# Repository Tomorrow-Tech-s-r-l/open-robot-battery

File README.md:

# ⚡ Open Robot Battery (ORB)

*An open-source power delivery module for makers and robotics, powered by Amperry powerbanks.*

*Humanoid robot powered by the ORB module.*

*Four-wheeled warehouse robot with ORB battery module.*

*Front PCB view.*

*Back PCB view.*

*ORB inverter-turtle prototype with power inverter integration.*

*ORB development kit prototype for mobile robot applications.*

---

## 📖 Introduction

The **Open Robot Battery** (codename **ORB**) is an open-source hardware module designed to power up robots, IoT devices, drones, and prototypes.  

It works with **Amperry powerbanks**, which are charged inside Amperry stations, and provides makers, startups, and research labs with a flexible, safe, and modular way to bring portable energy into their projects.  

> ⚠️ **Important**: To use ORB you need an **Amperry-compatible powerbank**, which must be purchased together with an Amperry station. The ORB module is open-source, but the powerbanks remain proprietary.

---

## 🚀 Features

- ✅ Open hardware design for makers, startups, and research labs  
- ✅ Modular connection system (pogo pins, solenoid lock)  
- ✅ Flexible output: USB-C PD, robotics connectors (XT30/XT60), barrel jacks, etc.  
- ✅ Adaptable form factor – attach to robots, kiosks, IoT devices  
- ✅ Safe and tested with Amperry powerbanks  

---

## 🔌 How It Works
[ Amperry Station ] → [ Powerbank ] → [ ORB Module ] → [ Your Device ]

1. Powerbanks are charged inside the **Amperry station**.  
2. The charged powerbank is docked into the **ORB module**.  
3. ORB adapts the energy and delivers it to your device via your preferred connector.  

---

## 📦 Hardware Requirements

- **Required**: Amperry powerbank (purchase with a station from [Amperry](https://amperry.me))  
- Supported power levels:  
  - 5V (USB devices, IoT sensors)  
  - 12V (embedded boards, routers)  
  - 20V (robots, laptops, drones)  
- Connectors: USB-C PD, XT60, barrel jack, GPIO headers (customizable)  

---

## 🛠 Getting Started

1. Order an **Amperry powerbank + station**.  
2. Clone/download this repository.  
3. Access the **hardware files** in the `hardware/` folder:
   - Review the **schematics** (`hardware/schematics/LANDER_schematics.pdf`)
   - Check the **BOM** (`hardware/bom/LANDER_BOM.csv`) for component sourcing
   - Download **gerber files** (`hardware/gerber/LANDER-gerber-files.zip`) for PCB manufacturing
   - Use **CAD files** (`hardware/cad/LANDER_project_311025.zip`) for mechanical design and KiCad source files
4. Build or 3D-print the ORB module.  
5. Add the connectors your project requires.  
6. Plug in your powerbank and start powering your device.

## 🔧 Using with KiCad

The ORB project includes complete KiCad source files for both schematics and PCB layout. Follow these steps to open and work with the project in KiCad:

### Opening the KiCad Project

1. **Extract the CAD files**:
   ```bash
   cd hardware/cad
   unzip LANDER_project_311025.zip
   ```

2. **Open in KiCad**:
   - Launch KiCad (version 8.0 or later recommended)
   - Go to **File → Open Project**
   - Navigate to the extracted folder and open `Amperry_robot.kicad_pro`

3. **Project Structure**:
   The KiCad project contains:
   - `Amperry_robot.kicad_sch` - Main schematic file
   - `inputs_sheet.kicad_sch` - Input section schematic
   - `mech_conn_sheet.kicad_sch` - Mechanical connector section schematic
   - `Amperry_robot.kicad_pcb` - PCB layout file

### Viewing Schematics

- Click **Open Schematic** (or press `Ctrl+E`) to view the electrical schematics
- The project uses hierarchical sheets - navigate between sheets using the **Hierarchy Navigator** (press `Ctrl+H`)
- Use the **Properties** panel (press `E` on a component) to view component details

### Viewing PCB Layout

- Click **Open PCB Editor** (or press `Ctrl+P`) to view the PCB layout
- Use **3D Viewer** (press `Alt+3`) to see a 3D visualization of the board
- Switch between front and back layers using the layer selector

### Making Modifications

1. **Before making changes**, create a new branch or fork the repository
2. **Modify schematics** as needed:
   - Add/remove components
   - Adjust component values
   - Modify connections
3. **Update PCB layout** if schematic changes affect the board:
   - Run **Tools → Update PCB from Schematic** (or press `F8`) to sync changes
   - Adjust component placement and routing as needed
4. **Generate new Gerber files**:
   - Go to **File → Fabrication Outputs → Gerbers**
   - Select all layers and click **Generate Drill Files**
   - Export files for manufacturing

### Exporting for Manufacturing

1. **Generate Gerbers**:
   - File → Fabrication Outputs → Gerbers
   - Ensure all layers are selected (F.Cu, B.Cu, F.Silkscreen, B.Silkscreen, F.Mask, B.Mask, Edge.Cuts)
   - Generate drill files (PTH and NPTH)

2. **Generate BOM**:
   - File → Fabrication Outputs → BOM
   - Export as CSV or use the built-in BOM tool

3. **Create 3D Model**:
   - File → Export → STEP
   - Useful for mechanical integration

### Tips for Contributors

- Always run **Electrical Rules Check** (ERC) before committing changes (Tools → ERC)
- Run **Design Rules Check** (DRC) for PCB changes (Tools → DRC)
- Keep component libraries updated
- Document any significant changes in commit messages
- Test schematic changes by regenerating and reviewing the PDF export

## 📋 Documentation

- **[Technical Manual](MANUAL.md)** - Complete technical documentation including assembly instructions, safety warnings, and usage guidelines
- **[Hardware Files](hardware/)** - All hardware design files organized by type:
  - **[Schematics](hardware/schematics/)** - Electrical schematics in PDF format
  - **[Gerber Files](hardware/gerber/)** - PCB manufacturing files
  - **[Bill of Materials](hardware/bom/)** - Complete BOM in CSV format
  - **[CAD Files](hardware/cad/)** - KiCad source files (.kicad_sch, .kicad_pcb), 3D mechanical models (STEP), and Gerber files
  - **[Images](images/)** - Project images and diagrams  

---

## 💡 Example Use Cases

- 🤖 Robotics platforms and mobile robots  
- 🚁 Drones and UAVs  
- 🌐 IoT devices and field instruments  
- 🏫 University labs and prototyping kits  
- 🖥 Portable kiosks and installations  

---

## 📜 License & Usage Rules

- ORB is released as **open-source hardware** (license: [CC BY-NC-SA]).  
- **Restrictions**:  
  - The **Amperry powerbank hardware is proprietary** and must be purchased from Amperry.  
  - Usage in **powerbank rental systems** is exclusive to Amperry.  
  - Usage in **defense or weapons applications** requires prior approval and a special license.  

- For complete license details, see [LICENSE.md](LICENSE.md).
---

## 🤝 Contributing

We welcome contributions from the community! Here's how you can help improve the Open Robot Battery project.

### How to Contribute

1. **Report Issues**:
   - Found a bug or have a suggestion? Open an issue on GitHub
   - Include as much detail as possible: steps to reproduce, expected vs actual behavior, relevant files

2. **Improve Documentation**:
   - Fix typos or clarify instructions
   - Add missing information or examples
   - Translate documentation to other languages
   - Improve code comments and docstrings

3. **Hardware Improvements**:
   - **KiCad Project**: Modify schematics or PCB layout using the provided KiCad files
     - Extract the CAD files from `hardware/cad/LANDER_project_REV_DATE.zip` to work on them
     - Make changes in a new branch
     - Run ERC (Electrical Rules Check) and DRC (Design Rules Check) before submitting
     - Export updated Gerber files and update the repository
     - **Before committing**: Re-zip the CAD project folder and delete the unzipped folder
       ```bash
       cd hardware/cad
       zip -r LANDER_project_REV_DATE.zip [extracted_folder_name]/
       rm -rf [extracted_folder_name]/
       ```
     - Only commit the `.zip` file, not the extracted project files
     - This keeps the repository clean and prevents versioning conflicts with KiCad temporary files
   - **Mechanical Design**: Improve casing, mounting options, or add new connector configurations
   - **Component Selection**: Suggest better components or alternatives in the BOM

4. **Submit Pull Requests**:
   - Fork the repository
   - Create a feature branch (`git checkout -b feature/amazing-feature`)
   - Make your changes and test thoroughly
   - Commit with clear messages (`git commit -m 'Add amazing feature'`)
   - Push to your fork (`git push origin feature/amazing-feature`)
   - Open a Pull Request with a clear description of changes

### Contribution Guidelines

- **Code/Hardware Changes**:
  - Follow existing project structure and naming conventions
  - Ensure all tests pass (if applicable)
  - Update documentation for any new features
  - Run ERC/DRC checks for KiCad changes

- **Documentation**:
  - Use clear, concise language
  - Include examples where helpful
  - Update the README if adding new features

- **Pull Request Process**:
  - Keep PRs focused on a single feature or fix
  - Reference related issues in your PR description
  - Be responsive to feedback and requested changes

### Areas Where We Need Help

- 🐛 **Bug Fixes**: Test the design and report any issues
- 🔌 **New Connectors**: Add support for additional connector types
- 📐 **Mechanical Designs**: Improve casing, mounting solutions, or create 3D printable parts
- 🌍 **Translations**: Translate documentation to other languages
- 📚 **Examples**: Create example projects and use cases
- 🔬 **Testing**: Test designs with different powerbanks and report results

### Share Your Projects

We love seeing what people build with ORB! Share your projects:
- Open an issue with photos and description
- Tag us on social media
- Contribute to the gallery section

Thank you for contributing to open-source hardware! 🎉  

---

## 🌍 Community & Contact

- 🌐 Website: [https://tomorrowtech.it/open-robot-battery.html](https://amperry.me)  
- ✉️ Email: sviluppo@tomorrowtech.it  

---

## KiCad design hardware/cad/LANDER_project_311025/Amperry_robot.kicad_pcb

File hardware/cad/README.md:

# CAD Files

This folder contains the mechanical design files for the Open Robot Battery (LANDER) project.

## Files

- `LANDER-CAD-files.zip` - Complete CAD package containing 3D mechanical models and source files for the LANDER module
- `LANDER-mechanical.step` - 3D mechanical model in STEP format [TODO]
- `LANDER-mechanical.stl` - 3D printable files for prototyping [TODO]

## Mechanical Features

- Powerbank docking mechanism
- Spring ejector system
- Solenoid mounting points
- Connector mounting areas
- Heat dissipation considerations

## 3D Printing

STL files are provided for rapid prototyping and testing of mechanical components.

> **Note**: Replace this README with actual CAD files when available.

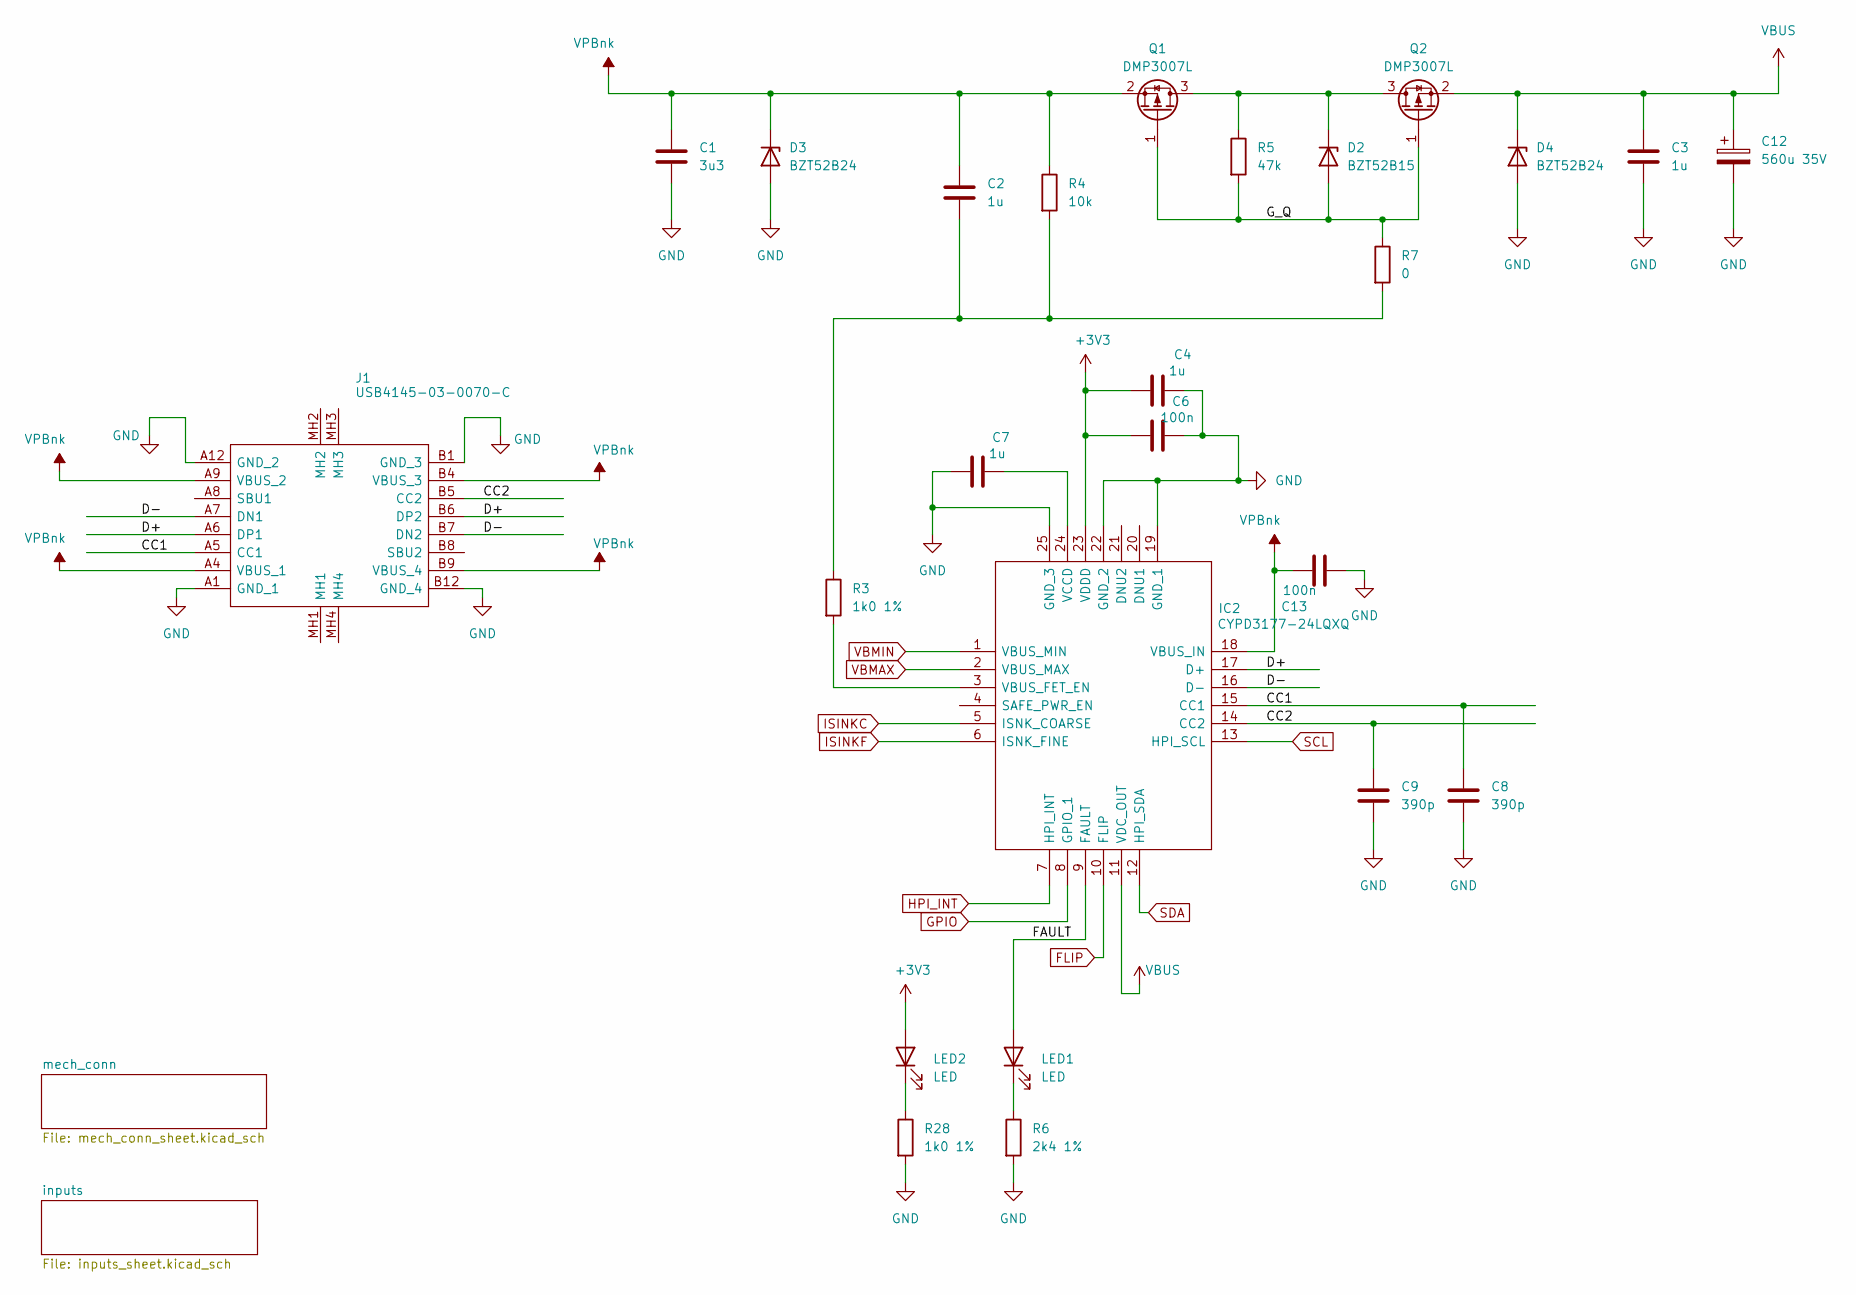
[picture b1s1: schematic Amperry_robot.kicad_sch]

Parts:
C1: 3u3; C_1206_3216Metric_Pad1.33x1.80mm_HandSolder
C2, C3, C4, C7: 1u; C_1206_3216Metric_Pad1.33x1.80mm_HandSolder
C6, C13: 100n; C_1206_3216Metric_Pad1.33x1.80mm_HandSolder
C8, C9: 390p; C_1206_3216Metric_Pad1.33x1.80mm_HandSolder
C12: 560u 35V; CP_Elec_10x10.5
D2: BZT52B15; D_SOD-123F
D3, D4: BZT52B24; D_SOD-123F
IC2: CYPD3177-24LQXQ; QFN50P400X400X60-25N-D; Manufacturer_Part_Number CYPD3177-24LQXQ; Mouser Part Number 727-CYPD3177-24LQXQ
J1: USB4145-03-0070-C; USB4145030070C; Manufacturer_Part_Number USB4145-03-0070-C; Mouser Part Number 640-USB4145-3-0070-C
LED1, LED2: LED; LED_0805_2012Metric_Pad1.15x1.40mm_HandSolder
Q1, Q2: DMP3007L; TO-252-2
R3, R28: 1k0 1%; R_1206_3216Metric_Pad1.30x1.75mm_HandSolder
R4: 10k; R_1206_3216Metric_Pad1.30x1.75mm_HandSolder
R5: 47k; R_1206_3216Metric_Pad1.30x1.75mm_HandSolder
R6: 2k4 1%; R_1206_3216Metric_Pad1.30x1.75mm_HandSolder
R7: 0; R_1206_3216Metric_Pad1.30x1.75mm_HandSolder

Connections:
+3V3: C4.2, C6.2, IC2.23 (VDDD), LED2.2 (A); also elsewhere on the board
/CC1: C8.1, IC2.15 (CC1), J1.A5 (CC1)
/CC2: C9.1, IC2.14 (CC2), J1.B5 (CC2)
/D+: IC2.17 (D+), J1.A6 (DP1), J1.B6 (DP2)
/D-: IC2.16 (D-), J1.A7 (DN1), J1.B7 (DN2)
/FAULT: IC2.9 (FAULT), LED1.2 (A)
/G_Q: D2.2 (A), Q1.1 (G), Q2.1 (G), R5.2, R7.1
FLIP: IC2.10 (FLIP); also elsewhere on the board
GND: C1.2, C3.2, C4.1, C6.1, C7.2, C8.2, C9.2, C12.2, C13.2, D3.2 (A), D4.2 (A), IC2.19 (GND_1), IC2.22 (GND_2), IC2.25 (GND_3), J1.A1 (GND_1), J1.A12 (GND_2), J1.B1 (GND_3), J1.B12 (GND_4), R6.2, R28.2; also elsewhere on the board
GPIO: IC2.8 (GPIO_1); also elsewhere on the board
HPI_INT: IC2.7 (HPI_INT); also elsewhere on the board
ISINKC: IC2.5 (ISNK_COARSE); also elsewhere on the board
ISINKF: IC2.6 (ISNK_FINE); also elsewhere on the board
unnamed: C2.2, R3.1, R4.2, R7.2
unnamed: D2.1 (K), Q1.3 (D), Q2.3 (D), R5.1
unnamed: IC2.3 (VBUS_FET_EN), R3.2
unnamed: C7.1, IC2.24 (VCCD)
unnamed: LED1.1 (K), R6.1
unnamed: LED2.1 (K), R28.1
SCL: IC2.13 (HPI_SCL); also elsewhere on the board
SDA: IC2.12 (HPI_SDA); also elsewhere on the board
VBMAX: IC2.2 (VBUS_MAX); also elsewhere on the board
VBMIN: IC2.1 (VBUS_MIN); also elsewhere on the board
VBUS: C3.1, C12.1, D4.1 (K), IC2.11 (VDC_OUT), Q2.2 (S); also elsewhere on the board
VPBnk: C1.1, C2.1, C13.1, D3.1 (K), IC2.18 (VBUS_IN), J1.A4 (VBUS_1), J1.A9 (VBUS_2), J1.B4 (VBUS_3), J1.B9 (VBUS_4), Q1.2 (S), R4.1; also elsewhere on the board

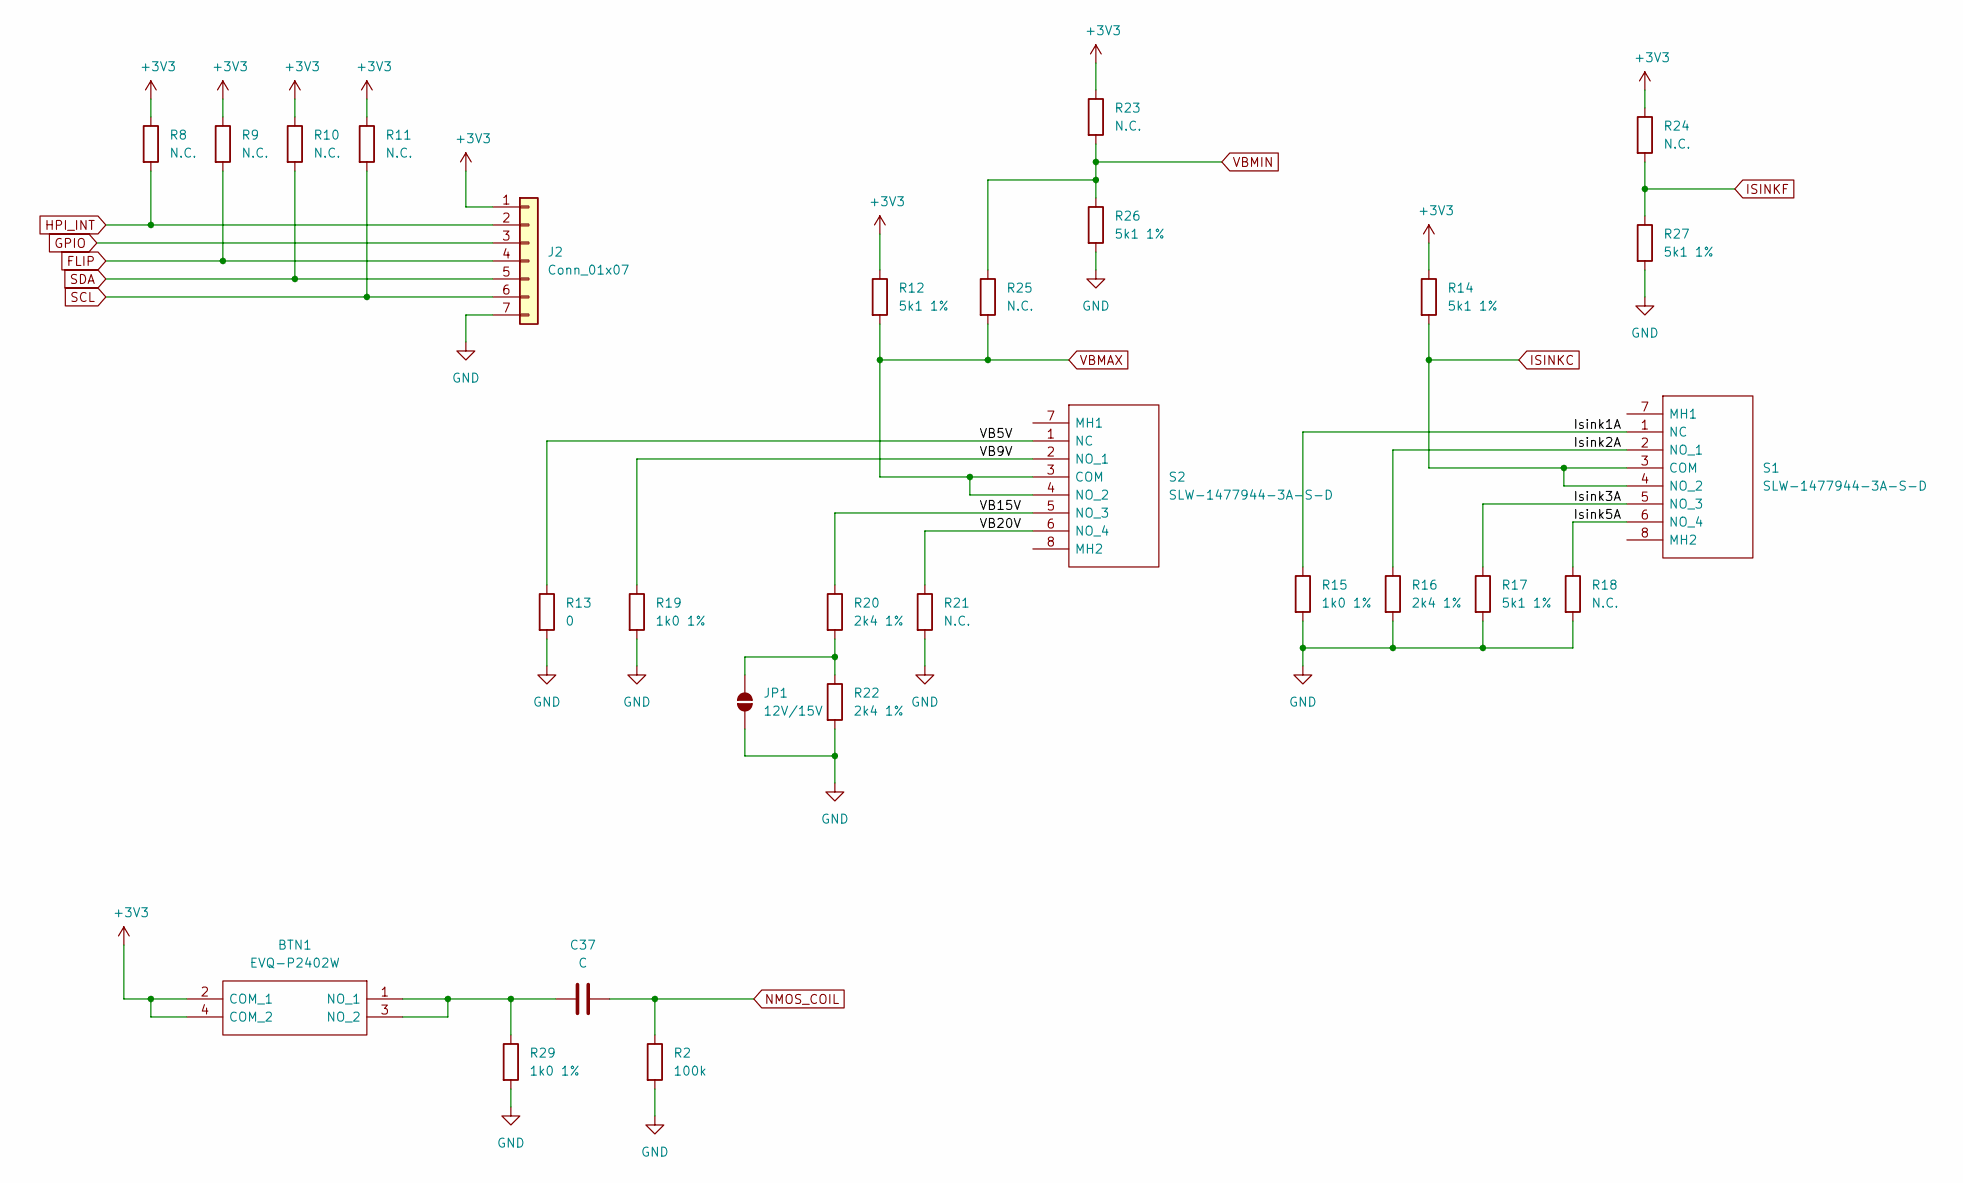
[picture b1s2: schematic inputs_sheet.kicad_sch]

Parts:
BTN1: EVQ-P2402W; EVQP2402W; Manufacturer_Part_Number EVQ-P2402W; Mouser Part Number 667-EVQ-P2402W
C37: C; C_1206_3216Metric_Pad1.33x1.80mm_HandSolder
J2: Conn_01x07; PinHeader_1x07_P2.54mm_Vertical
JP1: 12V/15V; SolderJumper-2_P1.3mm_Open_RoundedPad1.0x1.5mm
R2: 100k; R_1206_3216Metric_Pad1.30x1.75mm_HandSolder
R8, R9, R10, R11, R18, R21, R23, R24, R25: N.C.; R_1206_3216Metric_Pad1.30x1.75mm_HandSolder
R12, R14, R17, R26, R27: 5k1 1%; R_1206_3216Metric_Pad1.30x1.75mm_HandSolder
R13: 0; R_1206_3216Metric_Pad1.30x1.75mm_HandSolder
R15, R19, R29: 1k0 1%; R_1206_3216Metric_Pad1.30x1.75mm_HandSolder
R16, R20, R22: 2k4 1%; R_1206_3216Metric_Pad1.30x1.75mm_HandSolder
S1, S2: SLW-1477944-3A-S-D; SLW14779443ASD; Manufacturer_Part_Number SLW-1477944-3A-S-D; Mouser Part Number 179-SLW14779443ASD

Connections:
+3V3: BTN1.2 (COM_1), BTN1.4 (COM_2), J2.1, R8.1, R9.1, R10.1, R11.1, R12.1, R14.1, R23.1, R24.1; also elsewhere on the board
/inputs/Isink1A: R15.1, S1.1 (NC)
/inputs/Isink2A: R16.1, S1.2 (NO_1)
/inputs/Isink3A: R17.1, S1.5 (NO_3)
/inputs/Isink5A: R18.1, S1.6 (NO_4)
/inputs/VB5V: R13.1, S2.1 (NC)
/inputs/VB9V: R19.1, S2.2 (NO_1)
/inputs/VB15V: R20.1, S2.5 (NO_3)
/inputs/VB20V: R21.1, S2.6 (NO_4)
FLIP: J2.4, R9.2; also elsewhere on the board
GND: J2.7, JP1.1 (A), R2.2, R13.2, R15.2, R16.2, R17.2, R18.2, R19.2, R21.2, R22.2, R26.2, R27.2, R29.2; also elsewhere on the board
GPIO: J2.3; also elsewhere on the board
HPI_INT: J2.2, R8.2; also elsewhere on the board
ISINKC: R14.2, S1.3 (COM), S1.4 (NO_2); also elsewhere on the board
ISINKF: R24.2, R27.1; also elsewhere on the board
NMOS_COIL: C37.2, R2.1; also elsewhere on the board
unnamed: BTN1.1 (NO_1), BTN1.3 (NO_2), C37.1, R29.1
unnamed: JP1.2 (B), R20.2, R22.1
SCL: J2.6, R11.2; also elsewhere on the board
SDA: J2.5, R10.2; also elsewhere on the board
VBMAX: R12.2, R25.2, S2.3 (COM), S2.4 (NO_2); also elsewhere on the board
VBMIN: R23.2, R25.1, R26.1; also elsewhere on the board

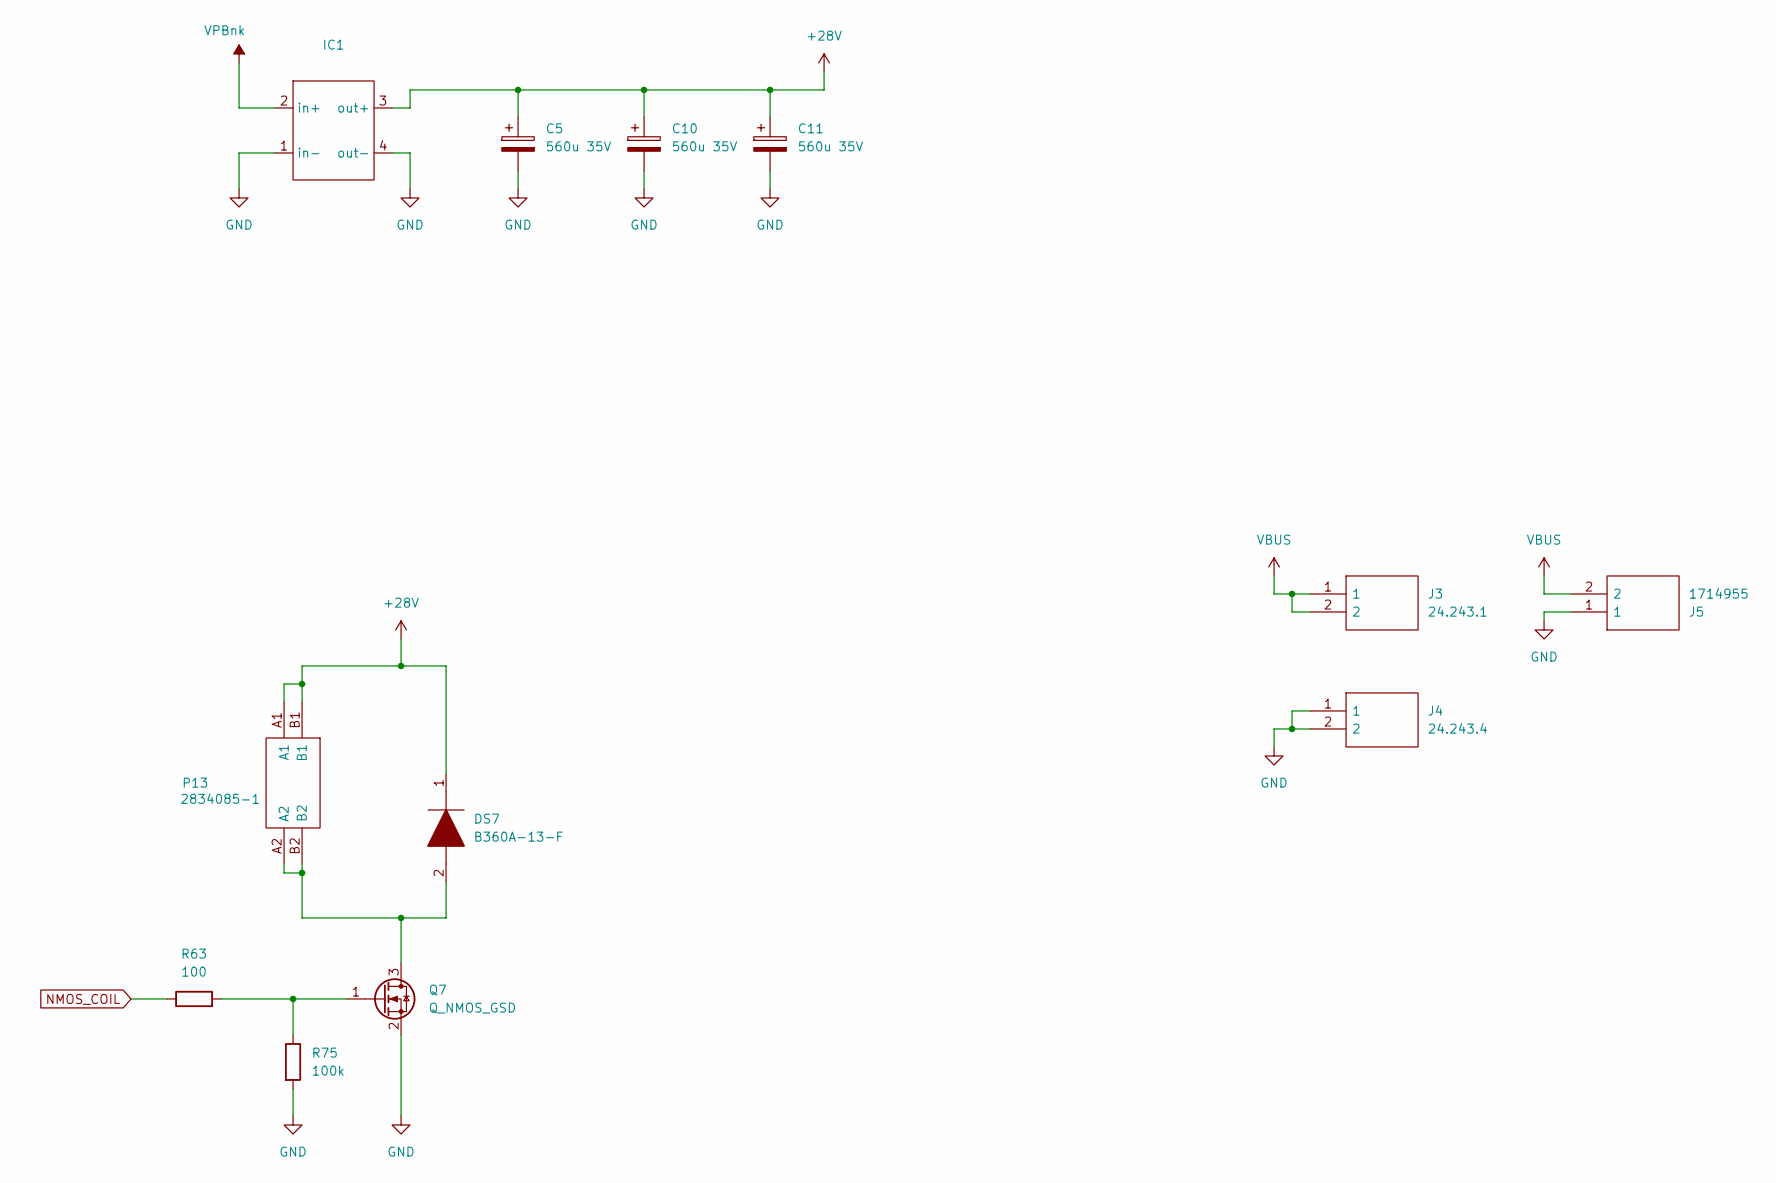
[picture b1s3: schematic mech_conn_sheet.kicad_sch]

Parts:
C5, C10, C11: 560u 35V; CP_Elec_10x10.5
DS7: B360A-13-F; DIOM5226X240N; Manufacturer_Part_Number B360A-13-F; Mouser Part Number 621-B360A-F
IC1: XL6009_boost
J3: 24.243.1; 242431; Manufacturer_Part_Number 24.243.1
J4: 24.243.4; 242434; Manufacturer_Part_Number 24.243.4
J5: 1714955; Manufacturer_Part_Number 1714955; Mouser Part Number 651-1714955
P13: 2834085-1; 28340851; Manufacturer_Part_Number 2834085-1; Mouser Part Number 571-2834085-1
Q7: Q_NMOS_GSD; SOT-23-3
R63: 100; R_1206_3216Metric_Pad1.30x1.75mm_HandSolder
R75: 100k; R_1206_3216Metric_Pad1.30x1.75mm_HandSolder

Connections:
+28V: C5.1, C10.1, C11.1, DS7.1, IC1.3 (out+), P13.A1, P13.B1
GND: C5.2, C10.2, C11.2, IC1.1 (in-), IC1.4 (out-), J4.1, J4.2, J5.1, Q7.2 (S), R75.2; also elsewhere on the board
NMOS_COIL: R63.1; also elsewhere on the board
unnamed: DS7.2, P13.A2, P13.B2, Q7.3 (D)
unnamed: Q7.1 (G), R63.2, R75.1
VBUS: J3.1, J3.2, J5.2; also elsewhere on the board
VPBnk: IC1.2 (in+); also elsewhere on the board

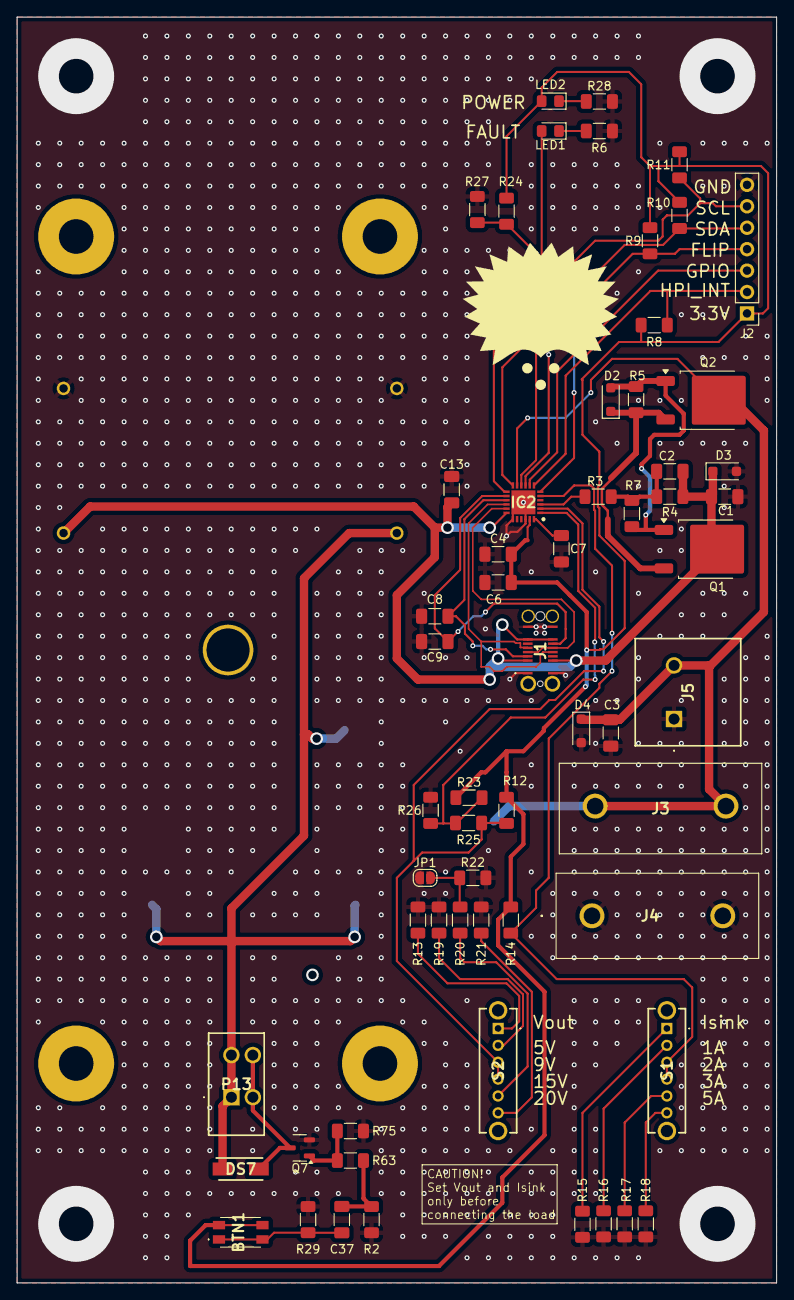
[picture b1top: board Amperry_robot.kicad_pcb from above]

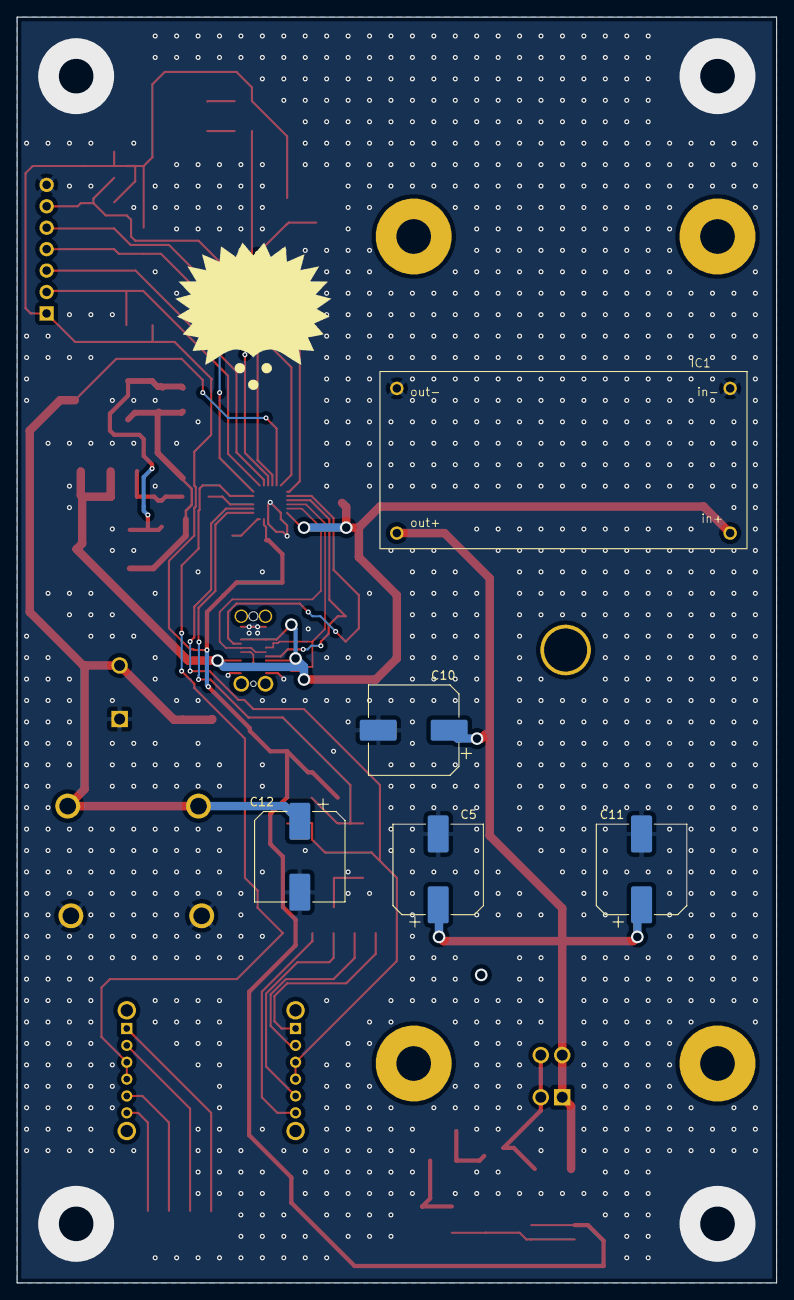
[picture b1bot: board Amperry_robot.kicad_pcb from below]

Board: 2 copper layers, 90.0 x 150.0 mm, 65 parts (4 on the bottom side), 39 nets.

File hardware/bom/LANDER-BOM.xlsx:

Comment | Description | Manufacturer_Part_Number | Manufacturer_Name | Designator | Footprint | Link mouser | Quantity
XL6009 boost module |  |  |  | IC1 | PCBComponent_1 | https://www.mouser.it/ProductDetail/Soldered/101600?qs=%252B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 | 1
USB4145-03-0070-C | Connector | USB4145-03-0070-C | GCT (GLOBAL CONNECTOR TECHNOLOGY) | J1 | USB4145030070C |  | 1
SQ2318AES-T1_BE3 | MOSFET N-CHANNEL 40V (D-S) 8 A SOT-23-3 |  |  | Q7 | SQ2318AES-T1_BE3-Footprint-1 |  | 1
SLW-1477944-3A-S-D | Switch | SLW-1477944-3A-S-D | Same Sky | S1, S6 | SLW14779443ASD |  | 2
NC | Not connected |  |  | R8, R9, R10, R11, R18, R21, R23, R24, R25 | res_1206 |  | 9
EVQ-P2402W | Switch | EVQ-P2402W | Panasonic | BTN1 | EVQP2402W |  | 1
EEE-FT1V561AP | Capacitor Polarised | EEE-FT1V561AP | Panasonic | C5, C10, C11, C12 | EEE0JA152UAP |  | 4
DMP3007LK3-13 | MOSFET (P-Channel) | DMP3007LK3-13 | Diodes Incorporated | Q1, Q2 | DMP3007LK313 |  | 2
CYPD3177-24LQXQ | Integrated Circuit | CYPD3177-24LQXQ | Infineon | IC2 | QFN50P400X400X60-25N-D |  | 1
BZT52C24-E3-08 | Zener Diode | BZT52C24-E3-08 | Vishay | D3, D4 | BZT52C24E308 |  | 2
BZT52C15-E3-08 | Zener Diode | BZT52C15-E3-08 | Vishay | D2 | SOD3716X135N |  | 1
APHCM2012CGCK-F01 | LED | APHCM2012CGCK-F01 | Kingbright | LED2 | LEDC2012X50N |  | 1
61300711121 | Connector | 61300711121 | Wurth Elektronik | J2 | HDRV7W64P0X254_1X7_1778X254X869P |  | 1
2834085-1 | Conn PC Terminal Block RCP 2 POS 2.54mm Solder Thru-Hole 4A/Contact Box/Carton |  |  | P13 | 2834085-1-Footprint-1 |  | 1
24.243.4 | Connector | 24.243.2 | Multicomp Pro | J4 | 242434 |  | 1
24.243.1 | Connector | 24.243.1 | Multicomp Pro | J3 | 242431 |  | 1
1714955 | Connector | 1714955 | Phoenix Contact | J5 | 1714955 |  | 1
NC | Not connected | 215931-0270 | Molex | J6 | 2159310270 |  | 1
150080SS75000 | LED | 150080SS75000 | Wurth Elektronik | LED1 | 150080SS75000 |  | 1
390p | Capacitor SMD | CC1206JRNPOBBN391 | Murata Elektronik | C8, C9 | cap_1206 |  | 2
100n | Capacitor SMD | KAF31BR71H104KT | KYOCERA AVX | C6, C13 | cap_1206 |  | 1
100k | Resistor SMD | RC1206FR-7W100KL | YAGEO | R2, R75 | res_1206 |  | 2
100 | Resistor SMD | RC1206FR-07100RL | YAGEO | R63 | res_1206 |  | 1
47k | Resistor SMD | RC1206FR-1347K5L | YAGEO | R5 | res_1206 |  | 1
10u 10V | Capacitor SMD | TM8R106K010UBA | Vishay / Sprague | C37 | cap_1206 |  | 1
10k | Resistor SMD | RC1206FR-0710KL | YAGEO | R4 | res_1206 |  | 1
5.1k 1% | Resistor SMD | RCC12065K10FKEA | YAGEO | R12, R14, R17, R26, R27 | res_1206 |  | 5
3.3u | Capacitor SMD | SMDTD04330XA00KT00 | WIMA | C1 | cap_1206 |  | 1
2.4k 1% | Resistor SMD | RC1206FR-7W2K4L | YAGEO | R6, R16, R20 | res_1206 |  | 3
1u | Capacitor SMD | C1206C105J3RAC | KEMET | C2, C3, C4, C7 | cap_1206 |  | 4
1.0k 1% | Resistor SMD | RC1206FR-7W1KL | YAGEO | R15, R19 | res_1206 |  | 2
1k | Resistor SMD | RC1206FR-7W1KL | YAGEO | R1, R3, R28 | res_1206 |  | 3
0R | Resistor SMD | RC1206FR-130RL | YAGEO | R7, R13, R22 | res_1206 |  | 3
B360A-13-F | 60V 3.0A SURFACE MOUNT SCHOTTKY BARRIER RECTIFIER |  |  | DS7 | SMA-DO-214AC |  | 1
 | M4 spacer +screw |  |  |  |  |  | 4
 | coil |  |  |  |  |  | 1
 | 3D plastic powerbank housing |  |  |  |  |  | 1
 | spring ejector |  |  |  |  |  | 1

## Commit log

2025-08-12 Update README.md
    Initial changes.
2025-08-12 Create LICENSE.md
    Added license.
2025-08-12 Update README.md
    updated email
2025-08-12 Update README.md
    Fixed repo
2025-09-12 Added first version of lander
2025-09-15 Added new logs and branding.
2025-09-23 Added robot images examples.
2025-09-23 Adjusted image size.
2025-10-15 updated design, solving hw bugs and updating labels and documentation
2025-10-19 First implementation of the ros2 and raspberry-pi usage.
2025-10-19 Refactor project structure by moving ROS 2 workspace to a new software directory and updating README links accordingly. Removed obsolete ROS 2 files and directories.
2025-10-19 Remove obsolete gallery section from README.md
2025-10-19 Add .gitignore with macOS and Python patterns
2025-10-19 Remove obsolete BOM and Gerber files for Amperry 2 module power bank project.
2025-10-31 Updated KiCad project files and documentation
2025-11-02 Update README.md with new image paths, enhance documentation for KiCad usage, and add contribution guidelines. Remove obsolete .DS_Store file and include new images for the ORB project.
2025-11-02 Remove obsolete files and documentation for the Amperry robot project, including all KiCad design files, images, and generated outputs. This cleanup ensures the repository is up-to-date and free of u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
2025-11-02 Enhance LICENSE.md with additional restrictions for ORB hardware usage and update README.md to reference complete license details. Improve contribution guidelines for CAD file management to maintain 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
2025-11-22 Add battery charging guide with temporary procedure
2025-11-23 Add ORB inverter-turtle and development kit images to README
2025-11-23 Added Images .
